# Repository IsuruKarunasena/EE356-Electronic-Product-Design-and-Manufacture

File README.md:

# EE356-Electronic-Product-Design-and-Manufacture
Designed and Manufactured an Automated Plant Condition Monitoring and Watering System

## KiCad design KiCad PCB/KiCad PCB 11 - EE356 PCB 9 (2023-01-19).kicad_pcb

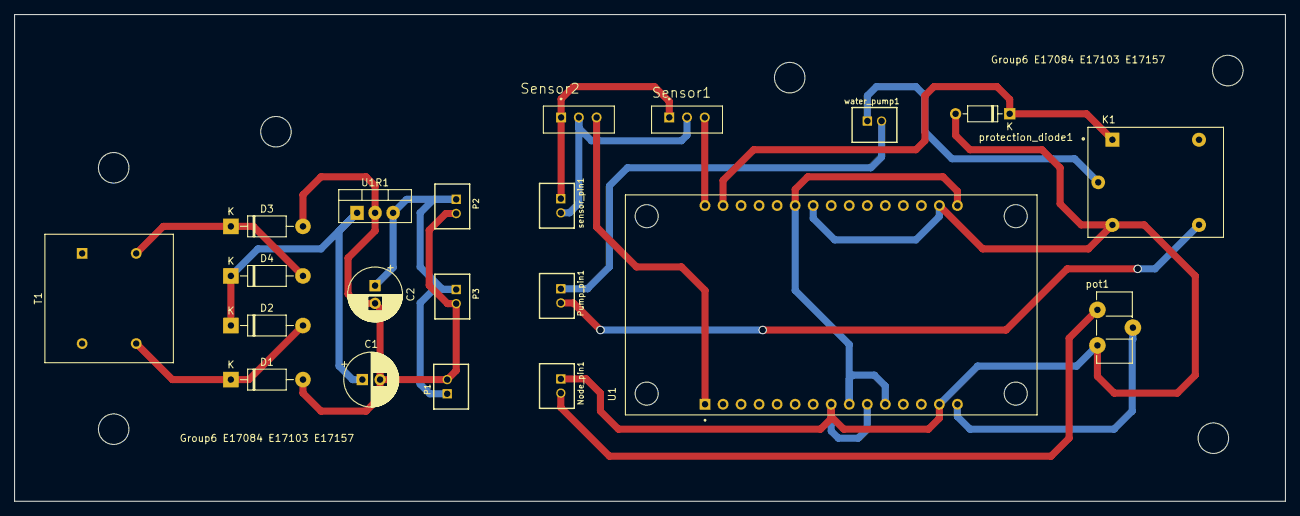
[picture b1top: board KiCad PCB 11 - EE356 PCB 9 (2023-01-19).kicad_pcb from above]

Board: 2 copper layers, 179.1 x 68.6 mm, 21 parts (0 on the bottom side), 17 nets.

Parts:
C1, C2: C_Polarized; CP_Radial_D7.5mm_P2.50mm
D1, D2, D3, D4: 1N4007; D_DO-41_SOD81_P10.16mm_Horizontal
K1: SRD-05VDC-SL-C; Relay SPDT Snapeda.com
Node_pin1: B2B-PH-K
P1, P2, P3: B2B-PH-K
Pump_pin1: B2B-PH-K
Sensor1, Sensor2: B3B-PH-K; TE_440052-3
T1: Transformer_1P_1S; Transformer_NF_ETAL_1-1_P1200
U1: VMA107; MODULE_VMA107
U1R1: L7805; TO-220-3_Vertical
pot1: R_Potentiometer; Potentiometer_ACP_CA9-H5_Horizontal
protection_diode1: 1N4148; D_DO-35_SOD27_P7.62mm_Horizontal
sensor_pin1: B2B-PH-K
water_pump1: B2B-PH-K

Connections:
/A0: Sensor2.3, U1.1 (A0)
/D0: Sensor1.3, U1.30 (D0)
/D1: K1.A1, U1.29 (D1), protection_diode1.1 (K)
/GND: K1.A2, Node_pin1.1, U1.8 (GND), U1.10 (GND), U1.14 (GND), U1.17 (GND), U1.24 (GND), pot1.3, protection_diode1.2 (A)
/Vin: U1.15 (5V), pot1.2
unnamed: C1.1, D2.1 (K), D4.1 (K), U1R1.1 (IN)
unnamed: C1.2, C2.2, D1.2 (A), D3.2 (A), P1.2, P2.2, P3.2, U1R1.2 (GND)
unnamed: C2.1, P1.1, P2.1, P3.1, U1R1.3 (OUT)
unnamed: D1.1 (K), D2.2 (A), T1.4 (SB)
unnamed: D3.1 (K), D4.2 (A), T1.3 (SA)
unnamed: K1.COM, water_pump1.1
unnamed: K1.NO, Pump_pin1.2
unnamed: Node_pin1.2, pot1.1
unnamed: Pump_pin1.1, water_pump1.2
unnamed: Sensor1.1, Sensor2.1, sensor_pin1.1
unnamed: Sensor1.2, Sensor2.2, sensor_pin1.2
unnamed: U1.9 (3V3), U1.11 (3V3), U1.16 (3V3), U1.25 (3V3)

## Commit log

2024-09-16 Create KiCad PCB 11 - EE356 PCB 9 (2023-01-19)
2024-09-16 Create Temp
